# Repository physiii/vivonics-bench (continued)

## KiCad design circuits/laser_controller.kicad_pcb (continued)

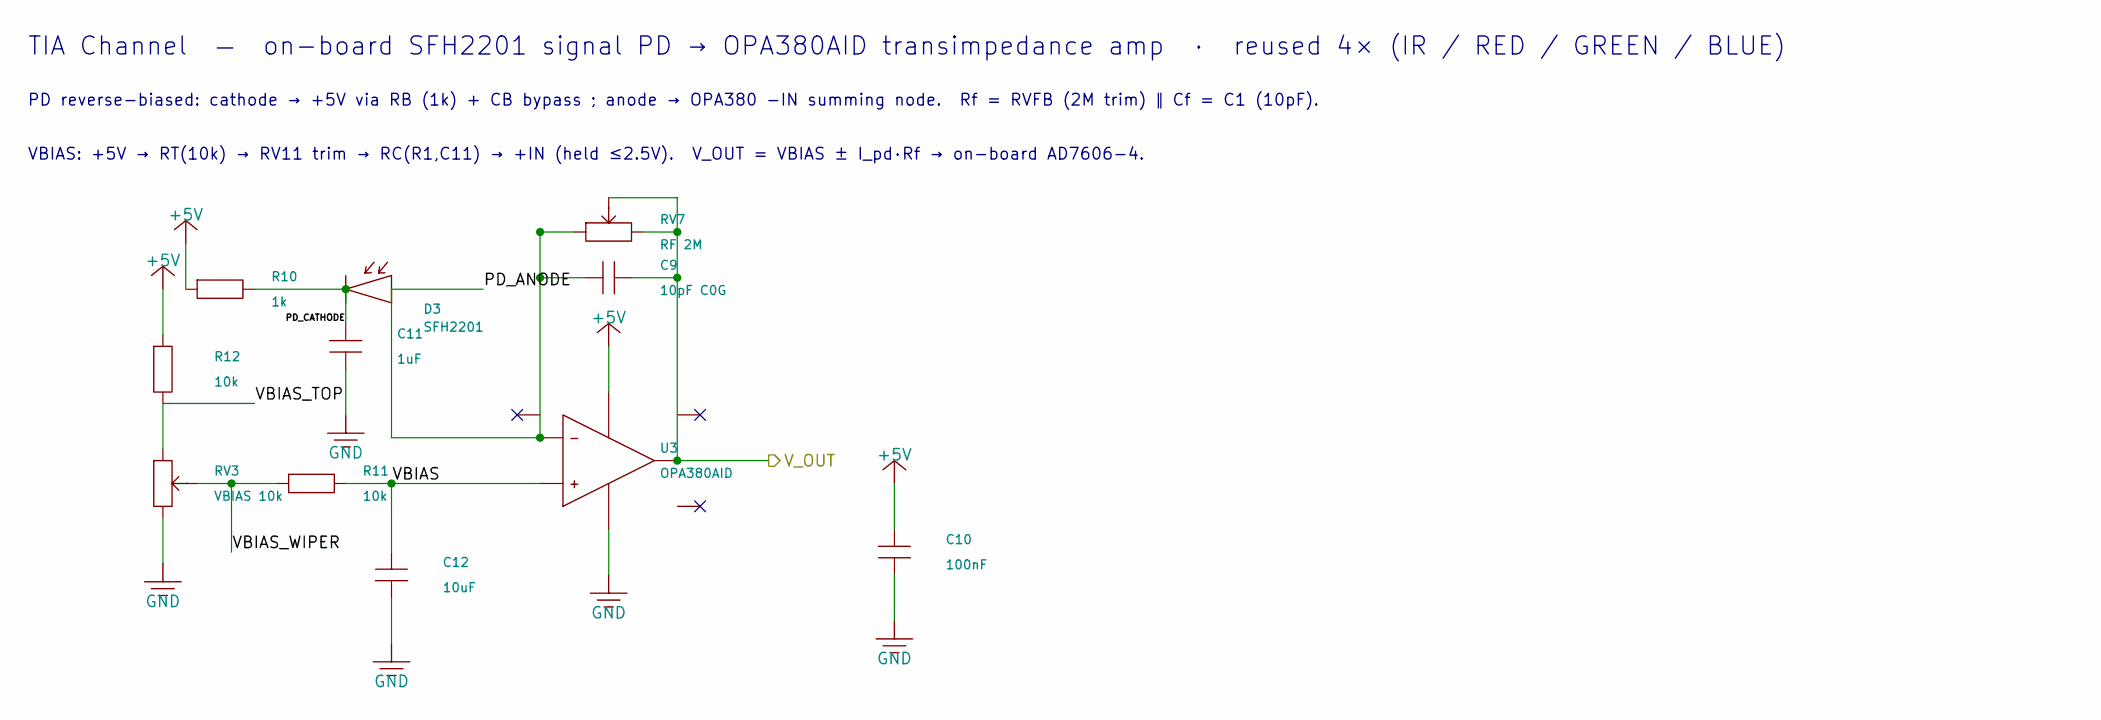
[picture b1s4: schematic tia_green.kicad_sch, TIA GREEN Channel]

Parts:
C9: 10pF C0G; C_0603_1608Metric_Pad1.08x0.95mm_HandSolder; Part Number CC0603JRNPO9BN100; LCSC C106245
C10: 100nF; C_0402_1005Metric_Pad0.74x0.62mm_HandSolder; Part Number 0402B104K160CT; LCSC C83056
C11: 1uF; C_0402_1005Metric_Pad0.74x0.62mm_HandSolder; Part Number HGC0402R5105K250NTEJ; LCSC C7472946
C12: 10uF; C_0805_2012Metric_Pad1.18x1.45mm_HandSolder; Part Number CL21A106KAYNNNG; LCSC C318691
D3: SFH2201; Osram_SFH2201; Part Number SFH2201; LCSC C2900216
R10: 1k; R_0603_1608Metric_Pad0.98x0.95mm_HandSolder; Part Number FRC0603F1001TS; LCSC C2907002
R11, R12: 10k; R_0603_1608Metric_Pad0.98x0.95mm_HandSolder; Part Number CRCW060310K0FKEA; LCSC C844918
RV3: VBIAS 10k; Potentiometer_Bourns_3224W_Vertical; Part Number 3224W-1-103E; LCSC C81348
RV7: RF 2M; Potentiometer_Bourns_3224W_Vertical; Part Number 3224W-1-205E; LCSC C116323
U3: OPA380AID; SOIC-8_3.9x4.9mm_P1.27mm; Part Number OPA380AID; LCSC C201677

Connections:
/TIA_GREEN/PD_ANODE: C9.1, D3.2 (A), RV7.1, U3.2 (-)
/TIA_GREEN/PD_CATHODE: C11.1, D3.1 (K), R10.2
/TIA_GREEN/VBIAS: C12.1, R11.2, U3.3 (+)
/TIA_GREEN/VBIAS_TOP: R12.2, RV3.1
/TIA_GREEN/VBIAS_WIPER: R11.1, RV3.2 (W)
VOUT3: C9.2, RV7.2 (W), RV7.3, U3.6; also elsewhere on the board

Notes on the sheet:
TIA Channel — on-board SFH2201 signal PD → OPA380AID transimpedance amp · reused 4× (IR / RED / GREEN / BLUE)
PD reverse-biased: cathode → +5V via RB (1k) + CB bypass ; anode → OPA380 −IN summing node. Rf = RVFB (2M trim) ∥ Cf = C1 (10pF).
VBIAS: +5V → RT(10k) → RV11 trim → RC(R1,C11) → +IN (held ≤2.5V). V_OUT = VBIAS ± I_pd·Rf → on-board AD7606-4.

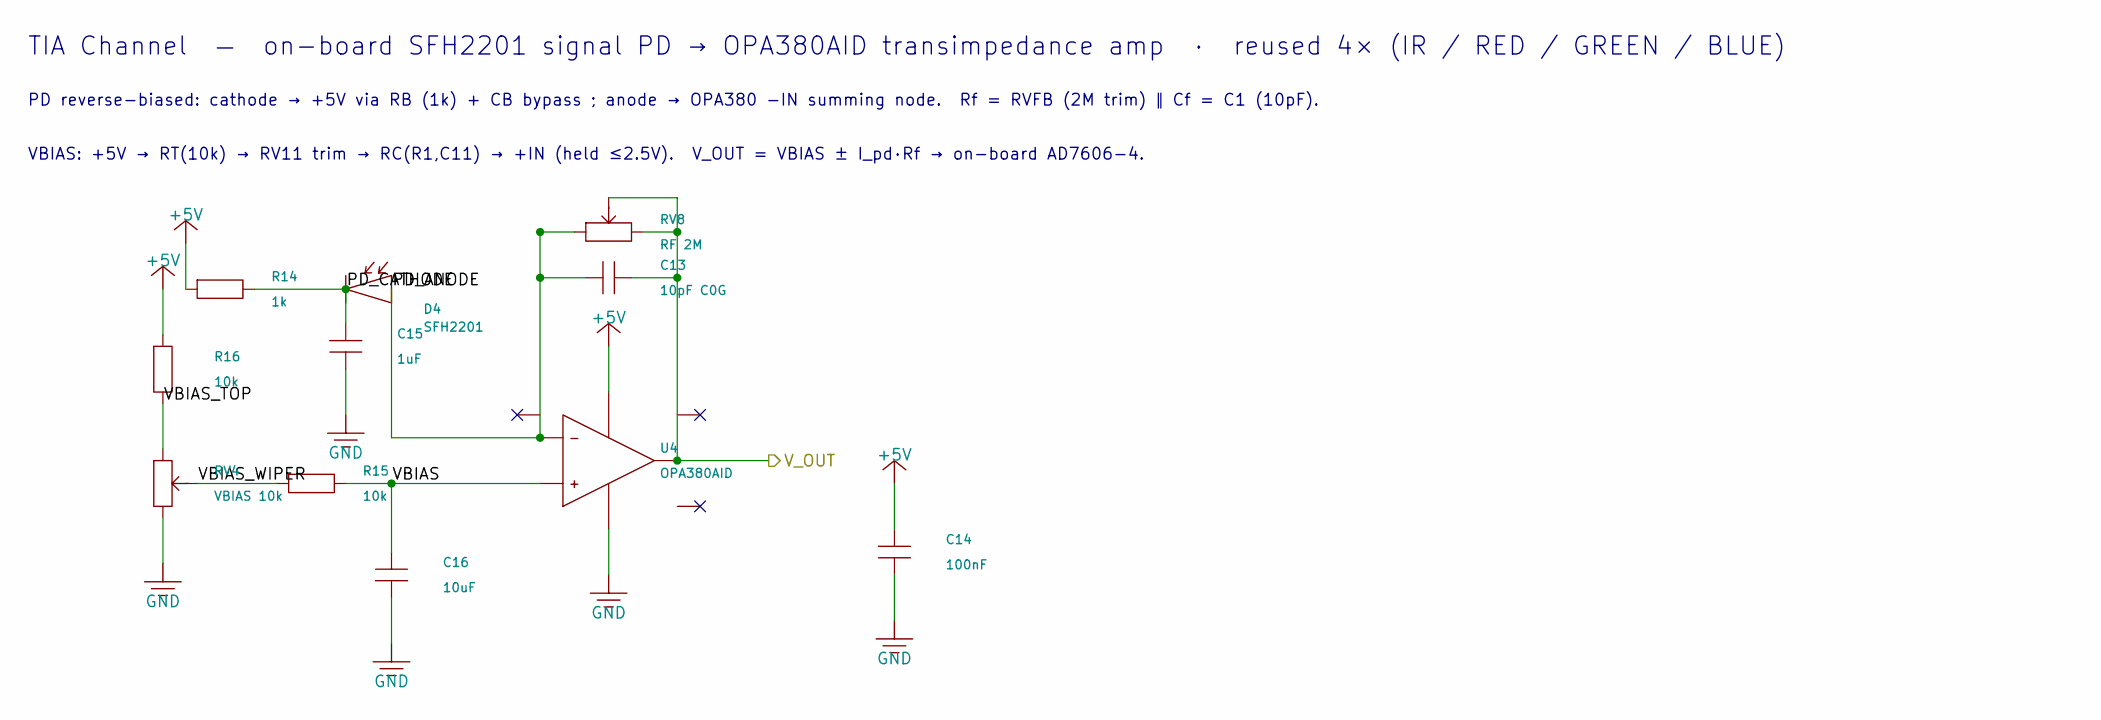
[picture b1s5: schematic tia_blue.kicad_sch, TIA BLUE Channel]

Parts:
C13: 10pF C0G; C_0603_1608Metric_Pad1.08x0.95mm_HandSolder; Part Number CC0603JRNPO9BN100; LCSC C106245
C14: 100nF; C_0402_1005Metric_Pad0.74x0.62mm_HandSolder; Part Number 0402B104K160CT; LCSC C83056
C15: 1uF; C_0402_1005Metric_Pad0.74x0.62mm_HandSolder; Part Number HGC0402R5105K250NTEJ; LCSC C7472946
C16: 10uF; C_0805_2012Metric_Pad1.18x1.45mm_HandSolder; Part Number CL21A106KAYNNNG; LCSC C318691
D4: SFH2201; Osram_SFH2201; Part Number SFH2201; LCSC C2900216
R14: 1k; R_0603_1608Metric_Pad0.98x0.95mm_HandSolder; Part Number FRC0603F1001TS; LCSC C2907002
R15, R16: 10k; R_0603_1608Metric_Pad0.98x0.95mm_HandSolder; Part Number CRCW060310K0FKEA; LCSC C844918
RV4: VBIAS 10k; Potentiometer_Bourns_3224W_Vertical; Part Number 3224W-1-103E; LCSC C81348
RV8: RF 2M; Potentiometer_Bourns_3224W_Vertical; Part Number 3224W-1-205E; LCSC C116323
U4: OPA380AID; SOIC-8_3.9x4.9mm_P1.27mm; Part Number OPA380AID; LCSC C201677

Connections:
/TIA_BLUE/PD_ANODE: C13.1, D4.2 (A), RV8.1, U4.2 (-)
/TIA_BLUE/PD_CATHODE: C15.1, D4.1 (K), R14.2
/TIA_BLUE/VBIAS: C16.1, R15.2, U4.3 (+)
/TIA_BLUE/VBIAS_TOP: R16.2, RV4.1
/TIA_BLUE/VBIAS_WIPER: R15.1, RV4.2 (W)
VOUT4: C13.2, RV8.2 (W), RV8.3, U4.6; also elsewhere on the board

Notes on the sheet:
TIA Channel — on-board SFH2201 signal PD → OPA380AID transimpedance amp · reused 4× (IR / RED / GREEN / BLUE)
PD reverse-biased: cathode → +5V via RB (1k) + CB bypass ; anode → OPA380 −IN summing node. Rf = RVFB (2M trim) ∥ Cf = C1 (10pF).
VBIAS: +5V → RT(10k) → RV11 trim → RC(R1,C11) → +IN (held ≤2.5V). V_OUT = VBIAS ± I_pd·Rf → on-board AD7606-4.

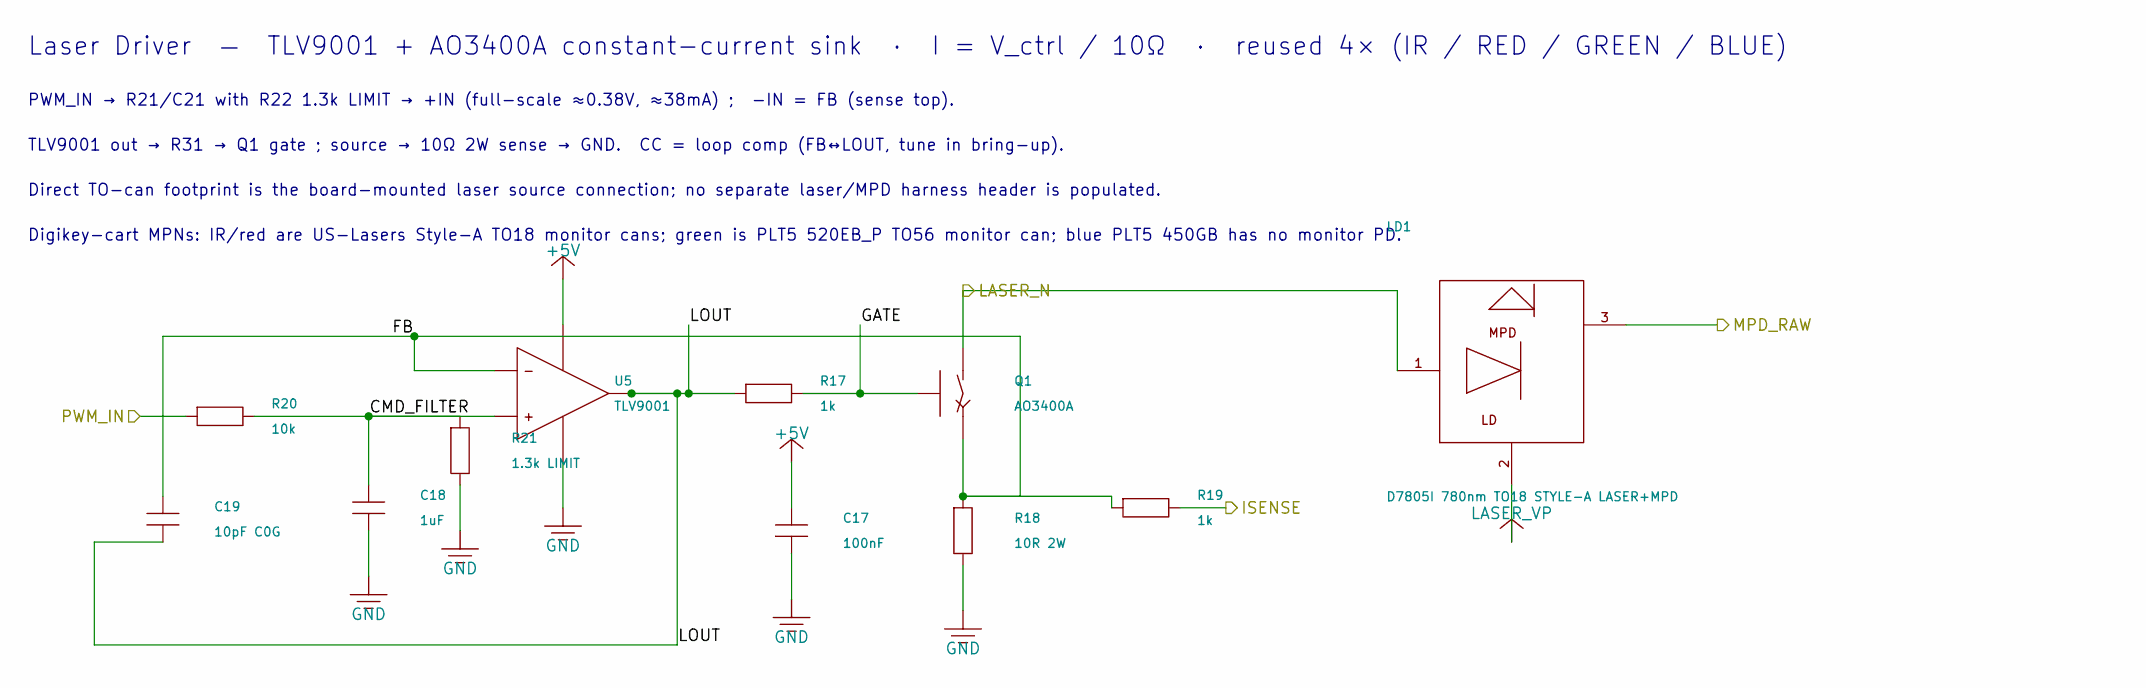
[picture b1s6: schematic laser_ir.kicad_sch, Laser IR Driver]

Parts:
C17: 100nF; C_0402_1005Metric_Pad0.74x0.62mm_HandSolder; Part Number 0402B104K160CT; LCSC C83056
C18: 1uF; C_0402_1005Metric_Pad0.74x0.62mm_HandSolder; Part Number HGC0402R5105K250NTEJ; LCSC C7472946
C19: 10pF C0G; C_0603_1608Metric_Pad1.08x0.95mm_HandSolder; Part Number CC0603JRNPO9BN100; LCSC C106245
LD1: D7805I 780nm TO18 STYLE-A LASER+MPD; LaserDiode_TO18-D5.6-3; Part Number D7805I
Q1: AO3400A; SOT-23; Part Number AO3400A; LCSC C20917
R17, R19: 1k; R_0603_1608Metric_Pad0.98x0.95mm_HandSolder; Part Number FRC0603F1001TS; LCSC C2907002
R18: 10R 2W; R_2512_6332Metric_Pad1.40x3.35mm_HandSolder; Part Number HoCR2512-2W-10R-1%; LCSC C5123624
R20: 10k; R_0603_1608Metric_Pad0.98x0.95mm_HandSolder; Part Number CRCW060310K0FKEA; LCSC C844918
R21: 1.3k LIMIT; R_0603_1608Metric_Pad0.98x0.95mm_HandSolder; Part Number 0603WAF1301T5E; LCSC C22767
U5: TLV9001; SOT-23-5; Part Number TLV9001IDBVR; LCSC C398363

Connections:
/LASER_IR/CMD_FILTER: C18.1, R20.2, R21.1, U5.3 (+)
/LASER_IR/FB: C19.1, Q1.2 (S), R18.1, R19.1, U5.4 (-)
/LASER_IR/GATE: Q1.1 (G), R17.2
/LASER_IR/LOUT: C19.2, R17.1, U5.1
ISENSE1: R19.2; also elsewhere on the board
LASER_N1: LD1.1 (LD_K), Q1.3 (D)
MPD_RAW1: LD1.3 (PD_A); also elsewhere on the board
PWM1: R20.1; also elsewhere on the board

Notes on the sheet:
Laser Driver — TLV9001 + AO3400A constant-current sink · I = V_ctrl / 10Ω · reused 4× (IR / RED / GREEN / BLUE)
PWM_IN → R21/C21 with R22 1.3k LIMIT → +IN (full-scale ≈0.38V, ≈38mA) ; −IN = FB (sense top).
TLV9001 out → R31 → Q1 gate ; source → 10Ω 2W sense → GND. CC = loop comp (FB↔LOUT, tune in bring-up).
Direct TO-can footprint is the board-mounted laser source connection; no separate laser/MPD harness header is populated.
Digikey-cart MPNs: IR/red are US-Lasers Style-A TO18 monitor cans; green is PLT5 520EB_P TO56 monitor can; blue PLT5 450GB has no monitor PD.

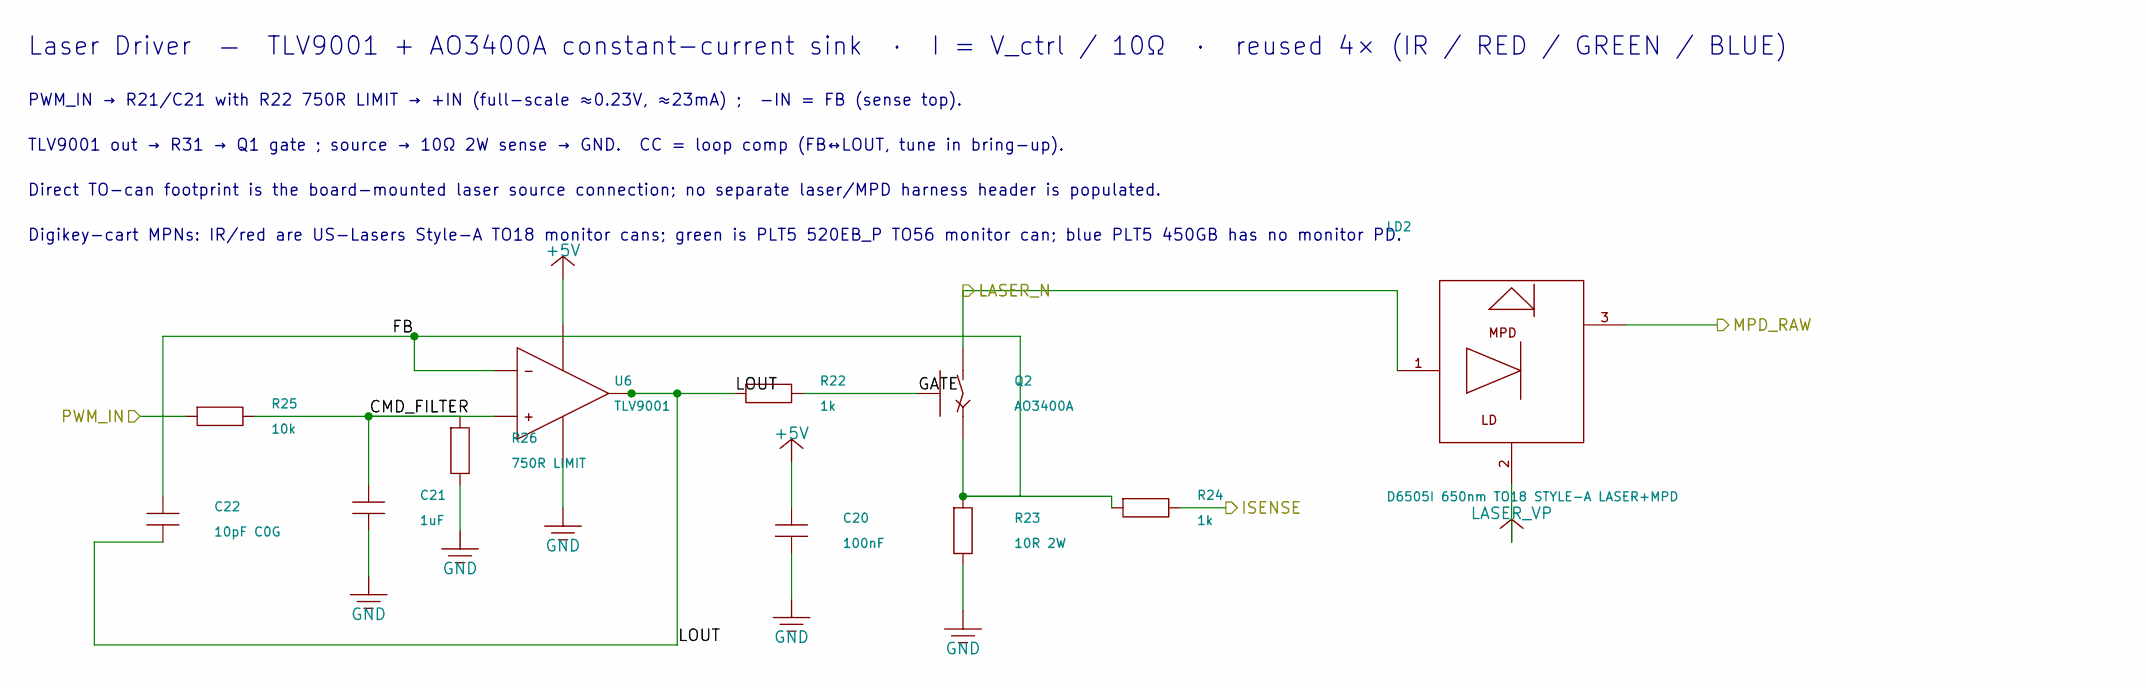
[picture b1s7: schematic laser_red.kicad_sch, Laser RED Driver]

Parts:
C20: 100nF; C_0402_1005Metric_Pad0.74x0.62mm_HandSolder; Part Number 0402B104K160CT; LCSC C83056
C21: 1uF; C_0402_1005Metric_Pad0.74x0.62mm_HandSolder; Part Number HGC0402R5105K250NTEJ; LCSC C7472946
C22: 10pF C0G; C_0603_1608Metric_Pad1.08x0.95mm_HandSolder; Part Number CC0603JRNPO9BN100; LCSC C106245
LD2: D6505I 650nm TO18 STYLE-A LASER+MPD; LaserDiode_TO18-D5.6-3; Part Number D6505I
Q2: AO3400A; SOT-23; Part Number AO3400A; LCSC C20917
R22, R24: 1k; R_0603_1608Metric_Pad0.98x0.95mm_HandSolder; Part Number FRC0603F1001TS; LCSC C2907002
R23: 10R 2W; R_2512_6332Metric_Pad1.40x3.35mm_HandSolder; Part Number HoCR2512-2W-10R-1%; LCSC C5123624
R25: 10k; R_0603_1608Metric_Pad0.98x0.95mm_HandSolder; Part Number CRCW060310K0FKEA; LCSC C844918
R26: 750R LIMIT; R_0603_1608Metric_Pad0.98x0.95mm_HandSolder; Part Number 0603WAF7500T5E; LCSC C23241
U6: TLV9001; SOT-23-5; Part Number TLV9001IDBVR; LCSC C398363

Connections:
/LASER_RED/CMD_FILTER: C21.1, R25.2, R26.1, U6.3 (+)
/LASER_RED/FB: C22.1, Q2.2 (S), R23.1, R24.1, U6.4 (-)
/LASER_RED/GATE: Q2.1 (G), R22.2
/LASER_RED/LOUT: C22.2, R22.1, U6.1
ISENSE2: R24.2; also elsewhere on the board
LASER_N2: LD2.1 (LD_K), Q2.3 (D)
MPD_RAW2: LD2.3 (PD_A); also elsewhere on the board
PWM2: R25.1; also elsewhere on the board

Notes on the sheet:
Laser Driver — TLV9001 + AO3400A constant-current sink · I = V_ctrl / 10Ω · reused 4× (IR / RED / GREEN / BLUE)
PWM_IN → R21/C21 with R22 750R LIMIT → +IN (full-scale ≈0.23V, ≈23mA) ; −IN = FB (sense top).
TLV9001 out → R31 → Q1 gate ; source → 10Ω 2W sense → GND. CC = loop comp (FB↔LOUT, tune in bring-up).
Direct TO-can footprint is the board-mounted laser source connection; no separate laser/MPD harness header is populated.
Digikey-cart MPNs: IR/red are US-Lasers Style-A TO18 monitor cans; green is PLT5 520EB_P TO56 monitor can; blue PLT5 450GB has no monitor PD.

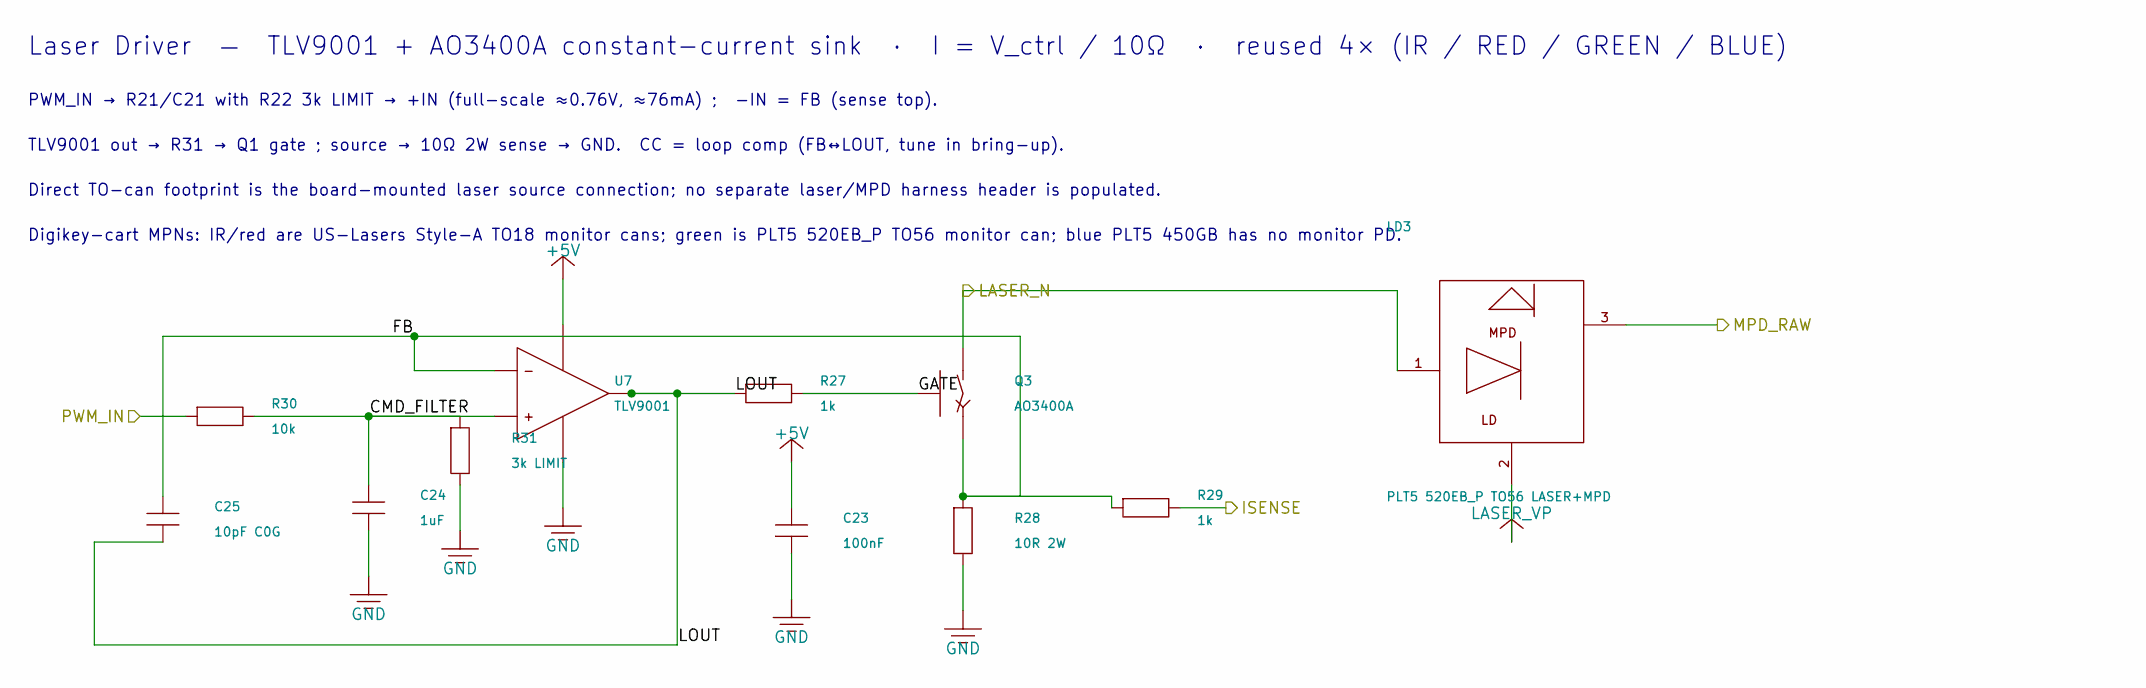
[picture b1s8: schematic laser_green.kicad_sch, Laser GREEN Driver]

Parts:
C23: 100nF; C_0402_1005Metric_Pad0.74x0.62mm_HandSolder; Part Number 0402B104K160CT; LCSC C83056
C24: 1uF; C_0402_1005Metric_Pad0.74x0.62mm_HandSolder; Part Number HGC0402R5105K250NTEJ; LCSC C7472946
C25: 10pF C0G; C_0603_1608Metric_Pad1.08x0.95mm_HandSolder; Part Number CC0603JRNPO9BN100; LCSC C106245
LD3: PLT5 520EB_P TO56 LASER+MPD; LaserDiode_TO56-3; Part Number PLT5 520EB_P
Q3: AO3400A; SOT-23; Part Number AO3400A; LCSC C20917
R27, R29: 1k; R_0603_1608Metric_Pad0.98x0.95mm_HandSolder; Part Number FRC0603F1001TS; LCSC C2907002
R28: 10R 2W; R_2512_6332Metric_Pad1.40x3.35mm_HandSolder; Part Number HoCR2512-2W-10R-1%; LCSC C5123624
R30: 10k; R_0603_1608Metric_Pad0.98x0.95mm_HandSolder; Part Number CRCW060310K0FKEA; LCSC C844918
R31: 3k LIMIT; R_0603_1608Metric_Pad0.98x0.95mm_HandSolder; Part Number 0603WAF3001T5E; LCSC C4211
U7: TLV9001; SOT-23-5; Part Number TLV9001IDBVR; LCSC C398363

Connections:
/LASER_GREEN/CMD_FILTER: C24.1, R30.2, R31.1, U7.3 (+)
/LASER_GREEN/FB: C25.1, Q3.2 (S), R28.1, R29.1, U7.4 (-)
/LASER_GREEN/GATE: Q3.1 (G), R27.2
/LASER_GREEN/LOUT: C25.2, R27.1, U7.1
ISENSE3: R29.2; also elsewhere on the board
LASER_N3: LD3.1 (LD_K), Q3.3 (D)
MPD_RAW3: LD3.3 (PD_A); also elsewhere on the board
PWM3: R30.1; also elsewhere on the board

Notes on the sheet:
Laser Driver — TLV9001 + AO3400A constant-current sink · I = V_ctrl / 10Ω · reused 4× (IR / RED / GREEN / BLUE)
PWM_IN → R21/C21 with R22 3k LIMIT → +IN (full-scale ≈0.76V, ≈76mA) ; −IN = FB (sense top).
TLV9001 out → R31 → Q1 gate ; source → 10Ω 2W sense → GND. CC = loop comp (FB↔LOUT, tune in bring-up).
Direct TO-can footprint is the board-mounted laser source connection; no separate laser/MPD harness header is populated.
Digikey-cart MPNs: IR/red are US-Lasers Style-A TO18 monitor cans; green is PLT5 520EB_P TO56 monitor can; blue PLT5 450GB has no monitor PD.

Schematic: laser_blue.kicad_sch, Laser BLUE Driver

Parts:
C26: 100nF; C_0402_1005Metric_Pad0.74x0.62mm_HandSolder; Part Number 0402B104K160CT; LCSC C83056
C27: 1uF; C_0402_1005Metric_Pad0.74x0.62mm_HandSolder; Part Number HGC0402R5105K250NTEJ; LCSC C7472946
C28: 10pF C0G; C_0603_1608Metric_Pad1.08x0.95mm_HandSolder; Part Number CC0603JRNPO9BN100; LCSC C106245
LD4: PLT5 450GB TO56 LASER CASE; LaserDiode_TO56-3; Part Number PLT5 450GB
Q4: AO3400A; SOT-23; Part Number AO3400A; LCSC C20917
R32, R34: 1k; R_0603_1608Metric_Pad0.98x0.95mm_HandSolder; Part Number FRC0603F1001TS; LCSC C2907002
R33: 10R 2W; R_2512_6332Metric_Pad1.40x3.35mm_HandSolder; Part Number HoCR2512-2W-10R-1%; LCSC C5123624
R35: 10k; R_0603_1608Metric_Pad0.98x0.95mm_HandSolder; Part Number CRCW060310K0FKEA; LCSC C844918
R36: 4.7k LIMIT; R_0603_1608Metric_Pad0.98x0.95mm_HandSolder; Part Number 0603WAF4701T5E; LCSC C23162
U8: TLV9001; SOT-23-5; Part Number TLV9001IDBVR; LCSC C398363

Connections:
/LASER_BLUE/CMD_FILTER: C27.1, R35.2, R36.1, U8.3 (+)
/LASER_BLUE/FB: C28.1, Q4.2 (S), R33.1, R34.1, U8.4 (-)
/LASER_BLUE/GATE: Q4.1 (G), R32.2
/LASER_BLUE/LOUT: C28.2, R32.1, U8.1
ISENSE4: R34.2; also elsewhere on the board
LASER_N4: LD4.3 (LD_K), Q4.3 (D)
PWM4: R35.1; also elsewhere on the board

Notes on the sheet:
Laser Driver — TLV9001 + AO3400A constant-current sink · I = V_ctrl / 10Ω · reused 4× (IR / RED / GREEN / BLUE)
PWM_IN → R21/C21 with R22 4.7k LIMIT → +IN (full-scale ≈1.06V, ≈106mA) ; −IN = FB (sense top).
TLV9001 out → R31 → Q1 gate ; source → 10Ω 2W sense → GND. CC = loop comp (FB↔LOUT, tune in bring-up).
Direct TO-can footprint is the board-mounted laser source connection; no separate laser/MPD harness header is populated.
Digikey-cart MPNs: IR/red are US-Lasers Style-A TO18 monitor cans; green is PLT5 520EB_P TO56 monitor can; blue PLT5 450GB has no monitor PD.

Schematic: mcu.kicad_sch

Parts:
C41, C42, C47: C_10uF; C_0805_2012Metric_Pad1.18x1.45mm_HandSolder; Part Number CL21A106KAYNNNG; LCSC C318691
C43: 100nF; C_0402_1005Metric_Pad0.74x0.62mm_HandSolder; Part Number 0402B104K160CT; LCSC C83056
C44, C45, C46: 1uF; C_0402_1005Metric_Pad0.74x0.62mm_HandSolder; Part Number HGC0402R5105K250NTEJ; LCSC C7472946
D7, D8, D9, D11, D12, D14: ESD_5V; D_SOD-523; Part Number LESD5D5.0CT1G(UMW); LCSC C5199850
D10, D13: D_1N5819HW; D_SOD-123; Part Number 1N5819HW-7-F; LCSC C82544
J1, J2: USB_MINI_B; USB_Mini-B_Wuerth_65100516121_Horizontal; Part Number 920-462A2021S10101; LCSC C46391
J7: C192300; PinHeader_2x04_P2.54mm_SMD_Vertical_C192300; Part Number 2.54-2*4P; LCSC C192300
Q5: Q_L8050QLT1G; SOT-23; Part Number L8050QLT1G; LCSC C49581
Q6: Q_L8550HQLT1G; SOT-23; Part Number L8550HQLT1G; LCSC C39282
R50, R51, R52, R53, R54, R58, R59, R60: 10K; R_0402_1005Metric_Pad0.72x0.64mm_HandSolder; Part Number ERJ2RKF1002X; LCSC C191123
R55: 22.1K; R_0402_1005Metric_Pad0.72x0.64mm_HandSolder; Part Number FRC0402F2212TS; LCSC C2929993
R56: 47.5K; R_0603_1608Metric_Pad0.98x0.95mm_HandSolder; Part Number 0603WAF4752T5E; LCSC C23061
R57: 1K; R_0402_1005Metric_Pad0.72x0.64mm_HandSolder; Part Number RT0402BRD071KL; LCSC C852624
SW1, SW2, SW3: SW_PUSH; SW_SPST_PTS645; Part Number K2-1102SP-C4SC-04; LCSC C127509
U9: ESP32-S3-WROOM-1; Part Number ESP32-S3-WROOM-1-N16; LCSC C2913199
U10: CP2102N-Axx-xQFN28; QFN-28-1EP_5x5mm_P0.5mm_EP3.35x3.35mm; Part Number CP2102N-A02-GQFN28R; LCSC C964632

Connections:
+3V3: C43.1, C47.1, J7.3 (+3V3), J7.4 (+3V3), R52.1, R53.1, R54.1, R57.1, R59.1, R60.2, U9.2 (3V3), U10.6 (VDD), U10.7 (VREGIN); also elsewhere on the board
/MCU_ESP32-S3/AUTO_BOOT_BASE: Q6.1 (B), R51.2
/MCU_ESP32-S3/AUTO_EN_BASE: Q5.1 (B), R50.2
/MCU_ESP32-S3/CP2102_RST: R57.2, U10.9 (~RST)
/MCU_ESP32-S3/CP2102_SUSPEND_N: R58.1, U10.11 (~SUSPEND)
/MCU_ESP32-S3/CP2102_VBUS: C45.1, R55.1, R56.2, U10.8 (VBUS)
/MCU_ESP32-S3/D+: D8.2 (A2), J1.3 (D+), U10.4 (D+)
/MCU_ESP32-S3/D-: D7.2 (A2), J1.2 (D-), U10.5 (D-)
/MCU_ESP32-S3/DTR: Q6.3 (C), R50.1, U10.28 (~DTR)
/MCU_ESP32-S3/EN: C44.1, Q5.3 (C), R54.2, SW1.1, U9.3 (EN)
/MCU_ESP32-S3/FACT: R52.2, SW3.1, U9.39 (GPIO1/TOUCH1/ADC1_CH0)
/MCU_ESP32-S3/IO13: R60.1, U9.21 (GPIO13/TOUCH13/ADC2_CH2/FSPIQ/FSPIIO7/S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)
/MCU_ESP32-S3/IO14: R59.2, U9.22 (GPIO14/TOUCH14/ADC2_CH3/FSPIWP/FSPIDQS/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)
/MCU_ESP32-S3/IO19: D12.2 (A2), J2.2 (D-), U9.13 (GPIO19/U1RTS/ADC2_CH8/CLK_OUT2/USB_D-)
/MCU_ESP32-S3/IO20: D11.2 (A2), J2.3 (D+), U9.14 (GPIO20/U1CTS/ADC2_CH9/CLK_OUT1/USB_D+)
/MCU_ESP32-S3/IO43: U9.37 (U0TXD/GPIO43/CLK_OUT1), U10.25 (RXD)
/MCU_ESP32-S3/IO44: U9.36 (U0RXD/GPIO44/CLK_OUT2), U10.26 (TXD)
/MCU_ESP32-S3/PROG: C46.1, Q6.2 (E), R53.2, SW2.1, U9.27 (GPIO0/BOOT)
/MCU_ESP32-S3/RTS: Q5.2 (E), R51.1, U10.24 (~RTS)
/MCU_ESP32-S3/USB_NATIVE_CONN_VBUS: D13.2 (A), J2.1 (VBUS)
/MCU_ESP32-S3/USB_UART_CONN_VBUS: D10.2 (A), J1.1 (VBUS)
ADC_BUSY: U9.24 (GPIO47/SPICLK_P/SUBSPICLK_P_DIFF); also elsewhere on the board
ADC_CS: U9.11 (GPIO18/U1RXD/ADC2_CH7/CLK_OUT3); also elsewhere on the board
ADC_MISO_A: U9.23 (GPIO21); also elsewhere on the board
ADC_MISO_B: U9.31 (GPIO38/FSPIWP/SUBSPIWP); also elsewhere on the board
ADC_RESET: U9.25 (GPIO48/SPICLK_N/SUBSPICLK_N_DIFF); also elsewhere on the board
ADC_SCLK: U9.10 (GPIO17/U1TXD/ADC2_CH6); also elsewhere on the board
CONVST: U9.8 (GPIO15/U0RTS/ADC2_CH4/XTAL_32K_P); also elsewhere on the board
ISENSE1: U9.4 (GPIO4/TOUCH4/ADC1_CH3); also elsewhere on the board
ISENSE2: U9.5 (GPIO5/TOUCH5/ADC1_CH4); also elsewhere on the board
ISENSE3: U9.6 (GPIO6/TOUCH6/ADC1_CH5); also elsewhere on the board
ISENSE4: U9.7 (GPIO7/TOUCH7/ADC1_CH6); also elsewhere on the board
MPD1: U9.38 (GPIO2/TOUCH2/ADC1_CH1); also elsewhere on the board
MPD2: U9.15 (GPIO3/TOUCH3/ADC1_CH2); also elsewhere on the board
MPD3: U9.12 (GPIO8/TOUCH8/ADC1_CH7/SUBSPICS1); also elsewhere on the board
MPD4: U9.17 (GPIO9/TOUCH9/ADC1_CH8/FSPIHD/SUBSPIHD); also elsewhere on the board
PWM1: U9.18 (GPIO10/TOUCH10/ADC1_CH9/FSPICS0/FSPIIO4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); also elsewhere on the board
PWM2: U9.19 (GPIO11/TOUCH11/ADC2_CH0/FSPID/FSPIIO5/S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); also elsewhere on the board
PWM3: U9.20 (GPIO12/TOUCH12/ADC2_CH1/FSPICLK/FSPIIO6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); also elsewhere on the board
PWM4: U9.9 (GPIO16/U0CTS/ADC2_CH5/XTAL_32K_N); also elsewhere on the board

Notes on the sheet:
J7 4x2 SMT power header (C192300): 1/2 GND, 3/4 +3V3, 5/6 +5V, 7/8 VIN_24V.

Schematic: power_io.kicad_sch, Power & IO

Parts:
C34: 10uF +5V bulk; C_0805_2012Metric_Pad1.18x1.45mm_HandSolder; Part Number CL21A106KAYNNNG; LCSC C318691
C35, C49: 100nF; C_0402_1005Metric_Pad0.74x0.62mm_HandSolder; Part Number 0402B104K160CT; LCSC C83056
C36: 100nF MPD bias; C_0402_1005Metric_Pad0.74x0.62mm_HandSolder; Part Number 0402B104K160CT; LCSC C83056
C37, C38, C39, C40: 100nF MPD ADC; C_0402_1005Metric_Pad0.74x0.62mm_HandSolder; Part Number 0402B104K160CT; LCSC C83056
C48: 1uF; C_0402_1005Metric_Pad0.74x0.62mm_HandSolder; Part Number HGC0402R5105K250NTEJ; LCSC C7472946
C50: 10uF; C_0805_2012Metric_Pad1.18x1.45mm_HandSolder; Part Number CL21A106KAYNNNG; LCSC C318691
C51, C52, C53, C54: 100nF ADC AVCC; C_0402_1005Metric_Pad0.74x0.62mm_HandSolder; Part Number 0402B104K160CT; LCSC C83056
C55: 100nF ADC VDRIVE; C_0402_1005Metric_Pad0.74x0.62mm_HandSolder; Part Number 0402B104K160CT; LCSC C83056
C56: 10uF ADC AVCC; C_0805_2012Metric_Pad1.18x1.45mm_HandSolder; Part Number CL21A106KAYNNNG; LCSC C318691
C57, C58: 1uF ADC REGCAP; C_0402_1005Metric_Pad0.74x0.62mm_HandSolder; Part Number HGC0402R5105K250NTEJ; LCSC C7472946
C59: 10uF ADC REF; C_0805_2012Metric_Pad1.18x1.45mm_HandSolder; Part Number CL21A106KAYNNNG; LCSC C318691
C60: 10uF ADC REFCAP; C_0805_2012Metric_Pad1.18x1.45mm_HandSolder; Part Number CL21A106KAYNNNG; LCSC C318691
C61, C62: 10uF 50V; C_1206_3216Metric_Pad1.33x1.80mm_HandSolder; Part Number CL31B106KBHNNNE; LCSC C89632
C63, C66: 100nF BST; C_0402_1005Metric_Pad0.74x0.62mm_HandSolder; Part Number 0402B104K160CT; LCSC C83056
C64, C65: 22uF 5V buck; C_0805_2012Metric_Pad1.18x1.45mm_HandSolder; Part Number CL21A226MAQNNNE; LCSC C45783
C67, C68: 22uF laser buck; C_0805_2012Metric_Pad1.18x1.45mm_HandSolder; Part Number CL21A226MAQNNNE; LCSC C45783
C69: 100pF FF; C_0402_1005Metric_Pad0.74x0.62mm_HandSolder; Part Number 0402CG101J500NT; LCSC C1546
C70: 22uF 100V; C_Elec_8x10.2; Part Number 100CE22FS+P; LCSC C242011
D5, D6: SS14; D_SMA; Part Number SS14; LCSC C2480
J5: 24V DC IN; BarrelJack_OD5.5_ID2.5; Part Number DC-470-2.1GP; LCSC C194407
J6: CONN_RJ45; RJ45_Amphenol_RJHSE538X; Part Number R-RJ45R08P-C000; LCSC C386757
L1: 4.7uH; L_5.4x5.3_H3; Part Number MWSA0503S-4R7MT; LCSC C408410
L2: 10uH; L_4x4; Part Number WPN4020H100MT; LCSC C98364
R41: 2.49k MPD bias; R_0603_1608Metric_Pad0.98x0.95mm_HandSolder; Part Number 0603WAF2491T5E; LCSC C22908
R42, R44, R46, R48: 240R MPD sense; R_0603_1608Metric_Pad0.98x0.95mm_HandSolder; Part Number RTT032400FTP; LCSC C103446
R43, R45, R47, R49: 1k ADC; R_0603_1608Metric_Pad0.98x0.95mm_HandSolder; Part Number FRC0603F1001TS; LCSC C2907002
R61: 237k FB; R_0603_1608Metric_Pad0.98x0.95mm_HandSolder; Part Number FRC0603F2373TS; LCSC C2998117
R62: 22.1K FB; R_0402_1005Metric_Pad0.72x0.64mm_HandSolder; Part Number FRC0402F2212TS; LCSC C2929993
R63, R64: 10K; R_0603_1608Metric_Pad0.98x0.95mm_HandSolder; Part Number CRCW060310K0FKEA; LCSC C844918
U11: AP2112K-3.3; SOT-23-5; Part Number AP2112K-3.3TRG1; LCSC C51118
U12: INA4180A1; TSSOP-14_4.4x5mm_P0.65mm; Part Number INA4180A1IPWR; LCSC C2057528
U13: LM4040C50 5V; SOT-23; Part Number LM4040C50IDBZR; LCSC C69316
U14: AD7606BSTZ-4; LQFP-64_10x10mm_P0.5mm; Part Number AD7606BSTZ-4RL; LCSC C51512
U15: AP63205WU-7 5V BUCK; TSOT-23-6; Part Number AP63205WU-7; LCSC C2071056
U16: AP63200WU-7 9.3V BUCK; TSOT-23-6; Part Number AP63200WU-7; LCSC C2071868

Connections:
+3V3: C35.1, C49.1, C50.1, C55.1, R64.1, U11.5 (VOUT), U12.4 (VS), U14.6 (PAR/SER/BYTE SEL), U14.7 (STBY), U14.23 (VDRIVE), U14.34 (REF SELECT); also elsewhere on the board
/POWER_IO/ADC_CREFIN: C59.1, U14.42 (REFIN/REFOUT)
/POWER_IO/ADC_CREG1: C57.1, U14.36 (REGCAP)
/POWER_IO/ADC_CREG2: C58.1, U14.39 (REGCAP)
/POWER_IO/ADC_REFCAP: C60.1, U14.44 (REFCAPA), U14.45 (REFCAPB)
/POWER_IO/BUCK5_BST: C63.2, U15.6 (BST)
/POWER_IO/BUCK5_SW: C63.1, L1.1, U15.5 (SW)
/POWER_IO/LASER_BUCK_BST: C66.2, U16.6 (BST)
/POWER_IO/LASER_BUCK_SW: C66.1, L2.1, U16.5 (SW)
/POWER_IO/MPD_AMP1: R43.1, U12.1 (OUT1)
/POWER_IO/MPD_AMP2: R45.1, U12.7 (OUT2)
/POWER_IO/MPD_AMP3: R47.1, U12.8 (OUT3)
/POWER_IO/MPD_AMP4: R49.1, U12.14 (OUT4)
/POWER_IO/MPD_BIAS: C36.2, R41.1, R42.2, R44.2, R46.2, R48.2, U12.2 (IN-1), U12.6 (IN-2), U12.9 (IN-3), U12.13 (IN-4), U13.2 (A), U13.3 (*)
/POWER_IO/RJ45_LED_CONTACT: J6.12, R64.2
/POWER_IO/RJ45_PWR_DETECT: J6.10, R63.2
ADC_BUSY: U14.14 (BUSY); also elsewhere on the board
ADC_CS: U14.13 (CS); also elsewhere on the board
ADC_MISO_A: U14.24 (DB7/DOUTA); also elsewhere on the board
ADC_MISO_B: U14.25 (DB8/DOUTB); also elsewhere on the board
ADC_RESET: U14.11 (RESET); also elsewhere on the board
ADC_SCLK: U14.12 (RD/SCLK); also elsewhere on the board
CONVST: U14.9 (CONVSTA), U14.10 (CONVSTB); also elsewhere on the board
MPD1: C37.1, R43.2; also elsewhere on the board
MPD2: C38.1, R45.2; also elsewhere on the board
MPD3: C39.1, R47.2; also elsewhere on the board
MPD4: C40.1, R49.2; also elsewhere on the board
MPD_RAW1: R42.1, U12.3 (IN+1); also elsewhere on the board
MPD_RAW2: R44.1, U12.5 (IN+2); also elsewhere on the board
MPD_RAW3: R46.1, U12.10 (IN+3); also elsewhere on the board
MPD_RAW4: R48.1, U12.12 (IN+4)
VOUT1: U14.49 (V1); also elsewhere on the board
VOUT2: U14.51 (V2); also elsewhere on the board
VOUT3: U14.57 (V3); also elsewhere on the board
VOUT4: U14.59 (V4); also elsewhere on the board

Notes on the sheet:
Power & I/O - 24V barrel/RJ45 input, onboard AP63205 +5V buck, AP63200 laser buck, AD7606-4 ADC, monitor-PD front end
Inputs: J5 barrel center and J6 pins 4/5 -> VIN_24V; J5 sleeve/switch and J6 pins 7/8/9/11 -> GND.
RJ45: copied access-controller CONN_RJ45 symbol; J6 pins 10/12 use 10k LED/contact resistors to VIN_24V/+3V3.
Supplies: U15 AP63205 -> BUCK_5V/+5V, U16 AP63200 -> LASER_V+ ~=9.3V; raw 24V stays off laser anodes.

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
